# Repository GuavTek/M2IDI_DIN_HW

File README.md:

This eurorack module is a gateway between MIDI 1.0 over a 5-pin DIN cable, and MIDI 2.0 over the internal bus.
View this project on [CADLAB.io](https://cadlab.io/project/25234) to see renders of schematics and PCBs, as well as current issues. 

<h2> A part of the M2IDI prototypes </h2>

<p>
The code for this module can be found on  
<a href="https://github.com/GuavTek/M2IDI_DIN">
			  GitHub
		  </a>
</p>

<p> 
More info on the M2IDI system can be found on the 
<a href="https://hackaday.io/project/182092-modular-midi">
			  Hackaday project page
		  </a>

</p>

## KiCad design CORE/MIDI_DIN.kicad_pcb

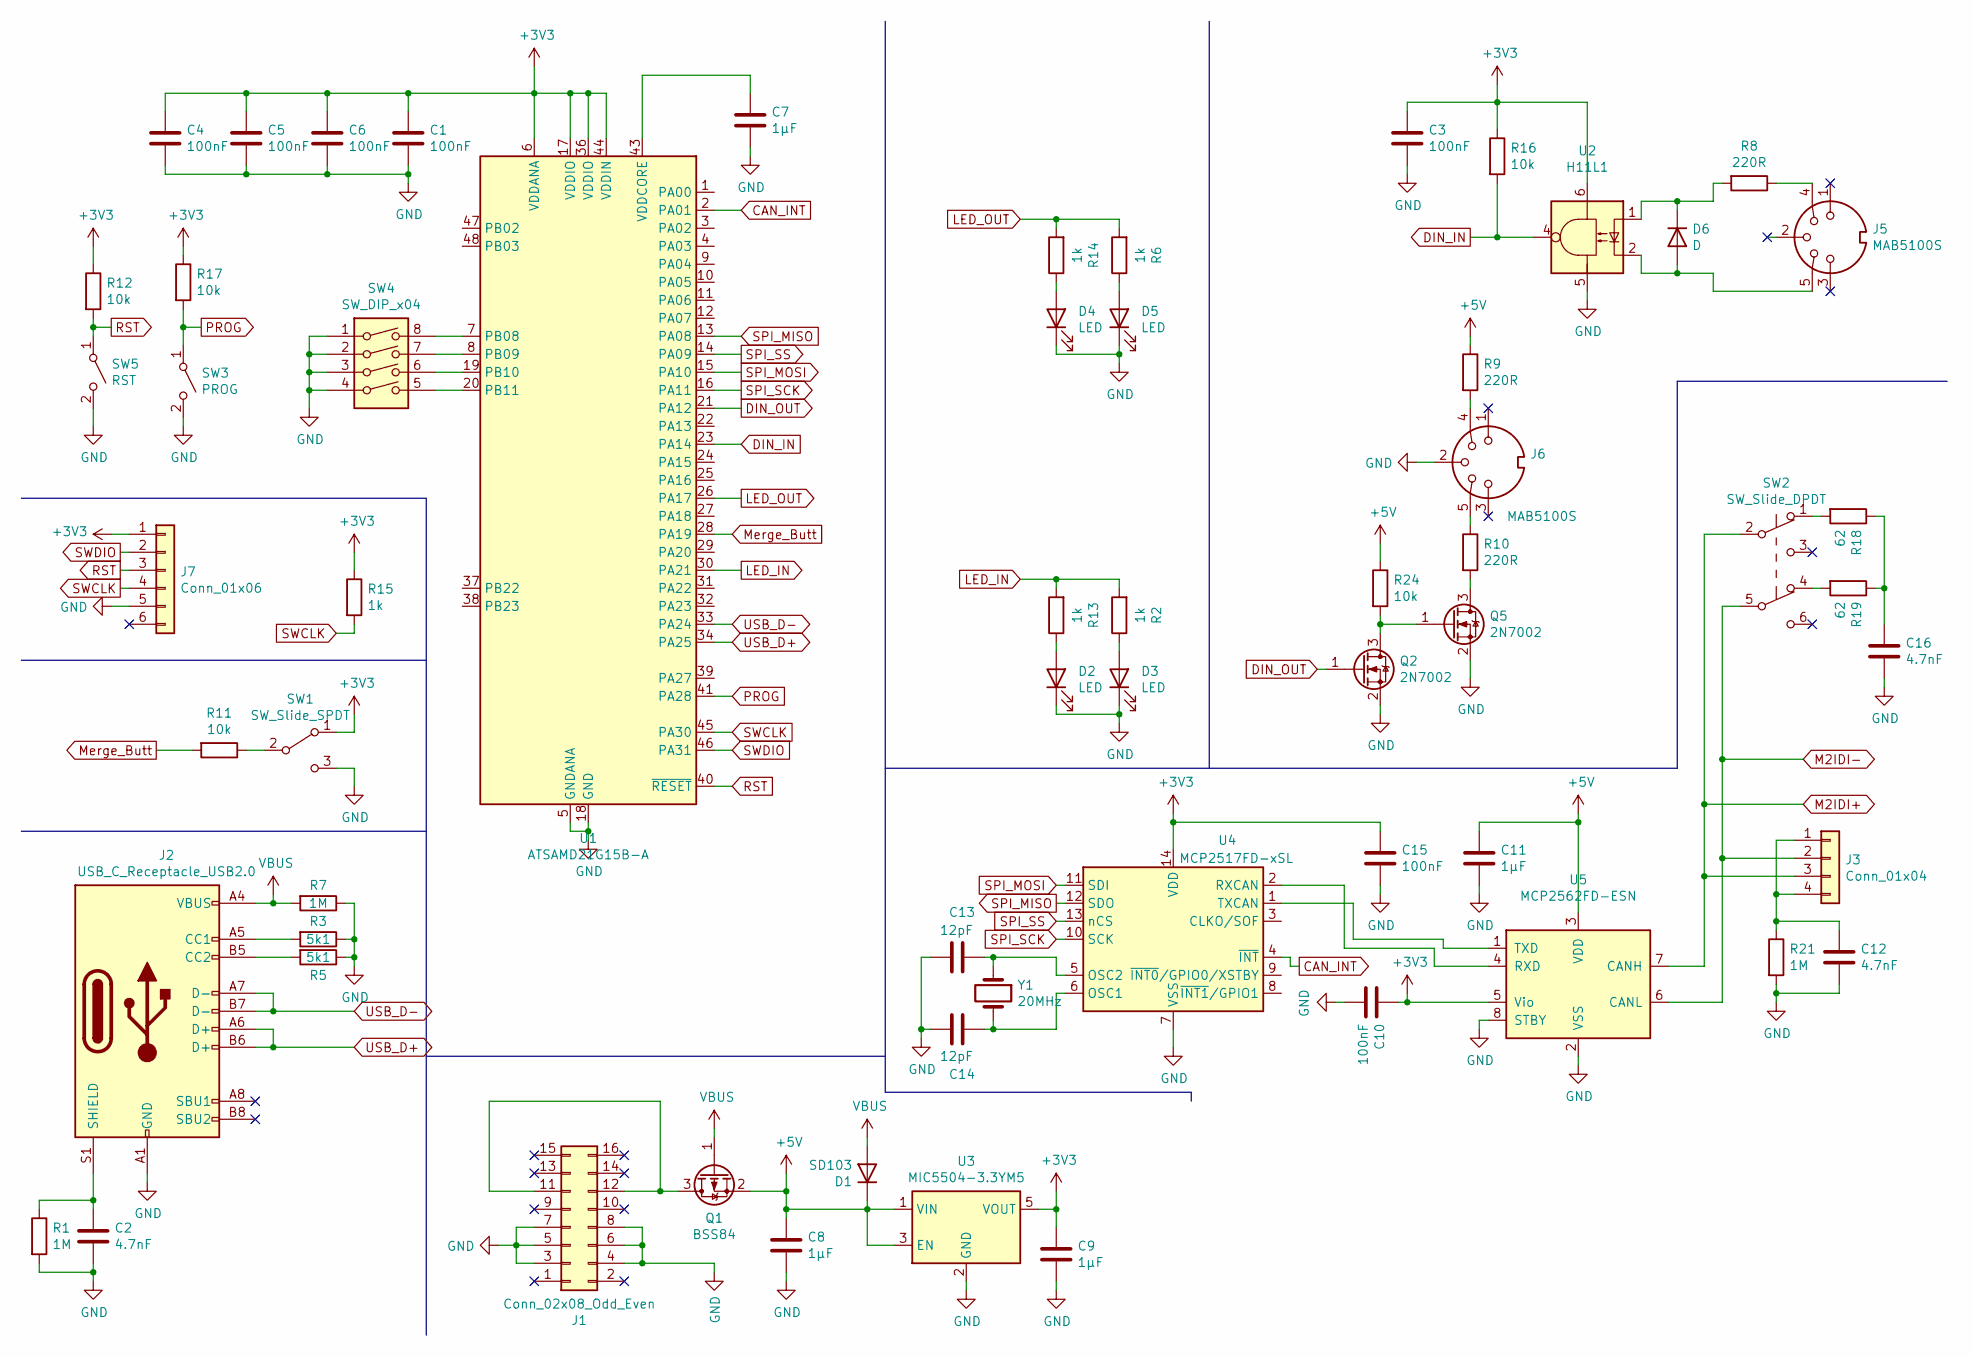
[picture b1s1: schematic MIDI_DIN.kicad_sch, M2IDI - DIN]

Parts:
C1, C3, C4, C5, C6, C10, C15: 100nF; C_0603_1608Metric
C2, C12, C16: 4.7nF; C_0603_1608Metric
C7, C8, C9, C11: 1µF; C_0603_1608Metric
C13, C14: 12pF; C_0603_1608Metric
D1: SD103; D_SOD-323_HandSoldering
D2, D3, D4, D5: LED; LED_D3.0mm
D6: D; D_SOD-323_HandSoldering
J1: Conn_02x08_Odd_Even; Header_2x8_Shrouded_SMD
J2: USB_C_Receptacle_USB2.0; USB_C_Receptacle_HRO_TYPE-C-31-M-12
J3: Conn_01x04; MicroMatch_04_Vertical_SMD_Lock
J5, J6: MAB5100S; DIN-5_Hirschmann
J7: Conn_01x06; TSM103-DH
Q1: BSS84; SOT-23
Q2, Q5: 2N7002; SOT-23
R1, R7, R21: 1M; R_0603_1608Metric
R2, R6, R13, R14, R15: 1k; R_0603_1608Metric
R3, R5: 5k1; R_0603_1608Metric
R8, R9, R10: 220R; R_0603_1608Metric
R11, R12, R16, R17, R24: 10k; R_0603_1608Metric
R18, R19: 62; R_0805_2012Metric
SW1: SW_Slide_SPDT; SlideSwitch-SS12D10
SW2: SW_Slide_DPDT; SlideDPDT_JS202011
SW3: PROG; Tactile_angled_5x5.4_SMD
SW4: SW_DIP_x04; SW_DIP_SPSTx04_Slide_Copal_CHS-04B_W7.62mm_P1.27mm
SW5: RST; Tactile_angled_5x5.4_SMD
U1: ATSAMD21G15B-A; TQFP-48_7x7mm_P0.5mm
U2: H11L1; DIP-6_W7.62mm_SMDSocket_SmallPads
U3: MIC5504-3.3YM5; SOT-23-5
U4: MCP2517FD-xSL; SOIC-14_3.9x8.7mm_P1.27mm
U5: MCP2562FD-ESN; SOIC-8_3.9x4.9mm_P1.27mm
Y1: 20MHz; Crystal_2pin_2.0x2.5mm

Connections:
+3V3: C1.1, C3.1, C4.1, C5.1, C6.1, C9.1, C10.1, C15.1, J7.1, R12.1, R15.1, R16.1, R17.1, SW1.1 (A), U1.6 (VDDANA), U1.17 (VDDIO), U1.36 (VDDIO), U1.44 (VDDIN), U2.6, U3.5 (VOUT), U4.14 (VDD), U5.5 (Vio)
+5V: C8.1, C11.1, D1.1 (K), Q1.2 (S), R9.1, R24.1, U3.1 (VIN), U3.3 (EN), U5.3 (VDD)
CAN_INT: U1.2 (PA01), U4.4 (~INT)
DIN_IN: R16.2, U1.23 (PA14), U2.4
DIN_OUT: Q2.1 (G), U1.21 (PA12)
GND: C1.2, C2.2, C3.2, C4.2, C5.2, C6.2, C7.2, C8.2, C9.2, C10.2, C11.2, C12.2, C13.2, C14.2, C15.2, C16.2, D2.1 (K), D3.1 (K), D4.1 (K), D5.1 (K), J1.3, J1.4, J1.5, J1.6, J1.7, J1.8, J2.A1 (GND), J2.A12 (GND), J2.B1 (GND), J2.B12 (GND), J6.2, J7.5, Q2.2 (S), Q5.2 (S), R1.2, R3.1, R5.1, R7.1, R21.2, SW1.3 (C), SW3.2 (B), SW4.1, SW4.2, SW4.3, SW4.4, SW5.2 (B), U1.5 (GNDANA), U1.18 (GND), U1.35 (GND), U1.42 (GND), U2.5, U3.2 (GND), U4.7 (VSS), U5.2 (VSS), U5.8 (STBY)
LED_IN: R2.2, R13.2, U1.30 (PA21)
LED_OUT: R6.2, R14.2, U1.26 (PA17)
M2IDI+: J3.3, SW2.2 (B), U5.7 (CANH)
M2IDI-: J3.2, SW2.5 (B), U5.6 (CANL)
Merge_Butt: R11.2, U1.28 (PA19)
unnamed: C16.1, R18.1, R19.1
unnamed: D2.2 (A), R13.1
unnamed: D3.2 (A), R2.1
unnamed: D4.2 (A), R14.1
unnamed: D5.2 (A), R6.1
unnamed: D6.2 (A), J5.5, U2.2
unnamed: D6.1 (K), R8.2, U2.1
unnamed: J1.11, J1.12, Q1.3 (D)
unnamed: J2.A5 (CC1), R3.2
unnamed: J2.B5 (CC2), R5.2
unnamed: C2.1, J2.S1 (SHIELD), R1.1
unnamed: C12.1, J3.1, J3.4, R21.1
unnamed: J5.4, R8.1
unnamed: J6.4, R9.2
unnamed: J6.5, R10.1
unnamed: Q2.3 (D), Q5.1 (G), R24.2
unnamed: Q5.3 (D), R10.2
unnamed: R18.2, SW2.1 (A)
unnamed: R19.2, SW2.4 (A)
unnamed: R11.1, SW1.2 (B)
unnamed: SW4.8, U1.7 (PB08)
unnamed: SW4.7, U1.8 (PB09)
unnamed: SW4.6, U1.19 (PB10)
unnamed: SW4.5, U1.20 (PB11)
unnamed: C7.1, U1.43 (VDDCORE)
unnamed: C14.1, U4.6 (OSC1), Y1.2
unnamed: C13.1, U4.5 (OSC2), Y1.1
unnamed: U4.2 (RXCAN), U5.4 (RXD)
unnamed: U4.1 (TXCAN), U5.1 (TXD)
PROG: R17.2, SW3.1 (A), U1.41 (PA28)
RST: J7.3, R12.2, SW5.1 (A), U1.40 (~RESET)
SPI_MISO: U1.13 (PA08), U4.12 (SDO)
SPI_MOSI: U1.15 (PA10), U4.11 (SDI)
SPI_SCK: U1.16 (PA11), U4.10 (SCK)
SPI_SS: U1.14 (PA09), U4.13 (nCS)
SWCLK: J7.4, R15.2, U1.45 (PA30)
SWDIO: J7.2, U1.46 (PA31)
USB_D+: J2.A6 (D+), J2.B6 (D+), U1.34 (PA25)
USB_D-: J2.A7 (D-), J2.B7 (D-), U1.33 (PA24)
VBUS: D1.2 (A), J2.A4 (VBUS), J2.A9 (VBUS), J2.B4 (VBUS), J2.B9 (VBUS), Q1.1 (G), R7.2

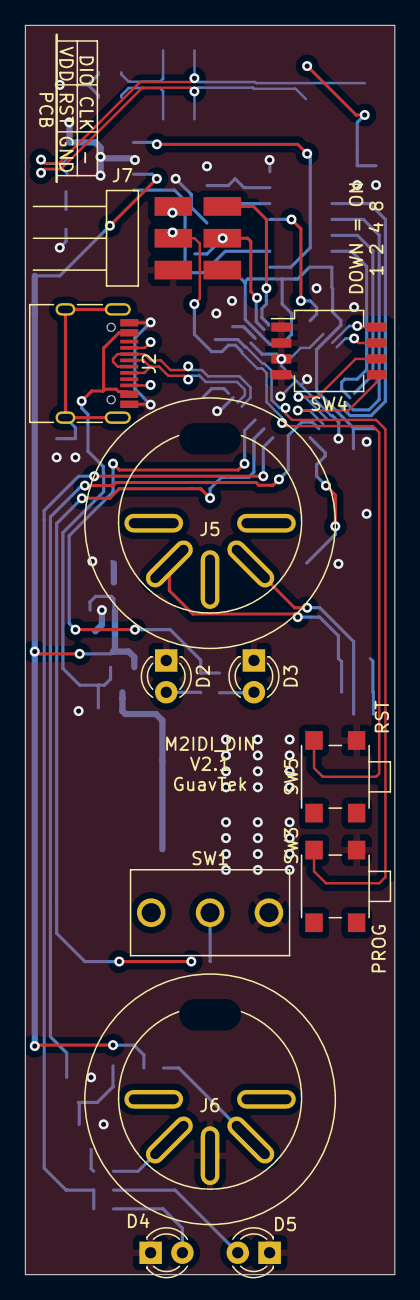
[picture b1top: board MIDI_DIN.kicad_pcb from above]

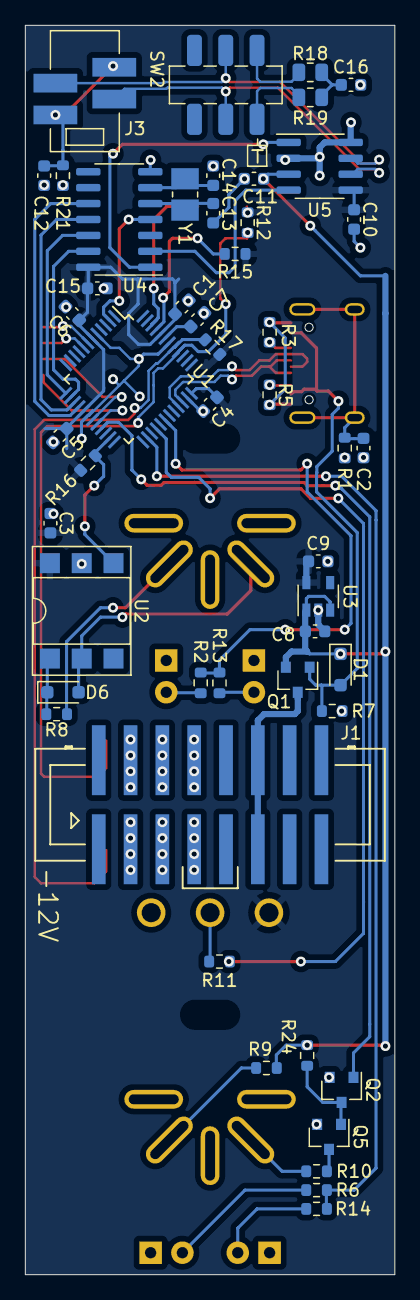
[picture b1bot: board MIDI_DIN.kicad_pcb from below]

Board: 2 copper layers, 29.5 x 99.8 mm, 62 parts (50 on the bottom side), 51 nets.

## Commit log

2022-02-17 Update License and Readme
2022-02-17 Add autogerber workflow
2022-02-17 Update termination values
2022-02-17 Fix paths
2022-02-17 Fix DRC errors
2022-02-17 Fix path again
2022-02-17 Backlink to CADLAB.io has been added.
2022-02-19 Add custom symbols and footprints
2022-12-31 Update PCB
    Fixed stuff
2022-12-31 Add horizontal prog header
2022-12-31 Make round slot corners
2023-03-17 Minor adjustments
2023-03-17 Update sheet metadata
2023-03-17 Update module name
2023-03-17 Move resistor out of the way
2023-03-18 Make room for latching connector
2023-03-19 Add 5V power protection
    Prevent USB connection from powering other modules
2023-03-19 Add pulldown for USB power protection
2023-04-04 Rearrange and re-wire
2023-04-08 Update front panel
2023-04-09 Switch to KiCAD 7
2023-04-09 Maybe fix autogerber action
2023-04-09 Change autogerber version
2023-04-09 Fix new DRC
2023-04-09 Ignore DRC warnings
2023-07-09 Change actions branch
2023-07-09 Change CAN tranceiver to MCP2562
2023-07-09 Fix 2x8 header footprint
2023-07-09 Fix crystal footprint
2023-07-09 Fix DRC warnings
2023-09-01 Finalize module
2023-09-16 Add warning about bootloader
2024-03-31 Switch from CC license to CERN open hardware
